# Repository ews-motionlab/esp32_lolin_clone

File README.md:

# esp32_lolin_clone
Design files for a PCB replicating the functionality and shape of the ESP32 lolin32 board.

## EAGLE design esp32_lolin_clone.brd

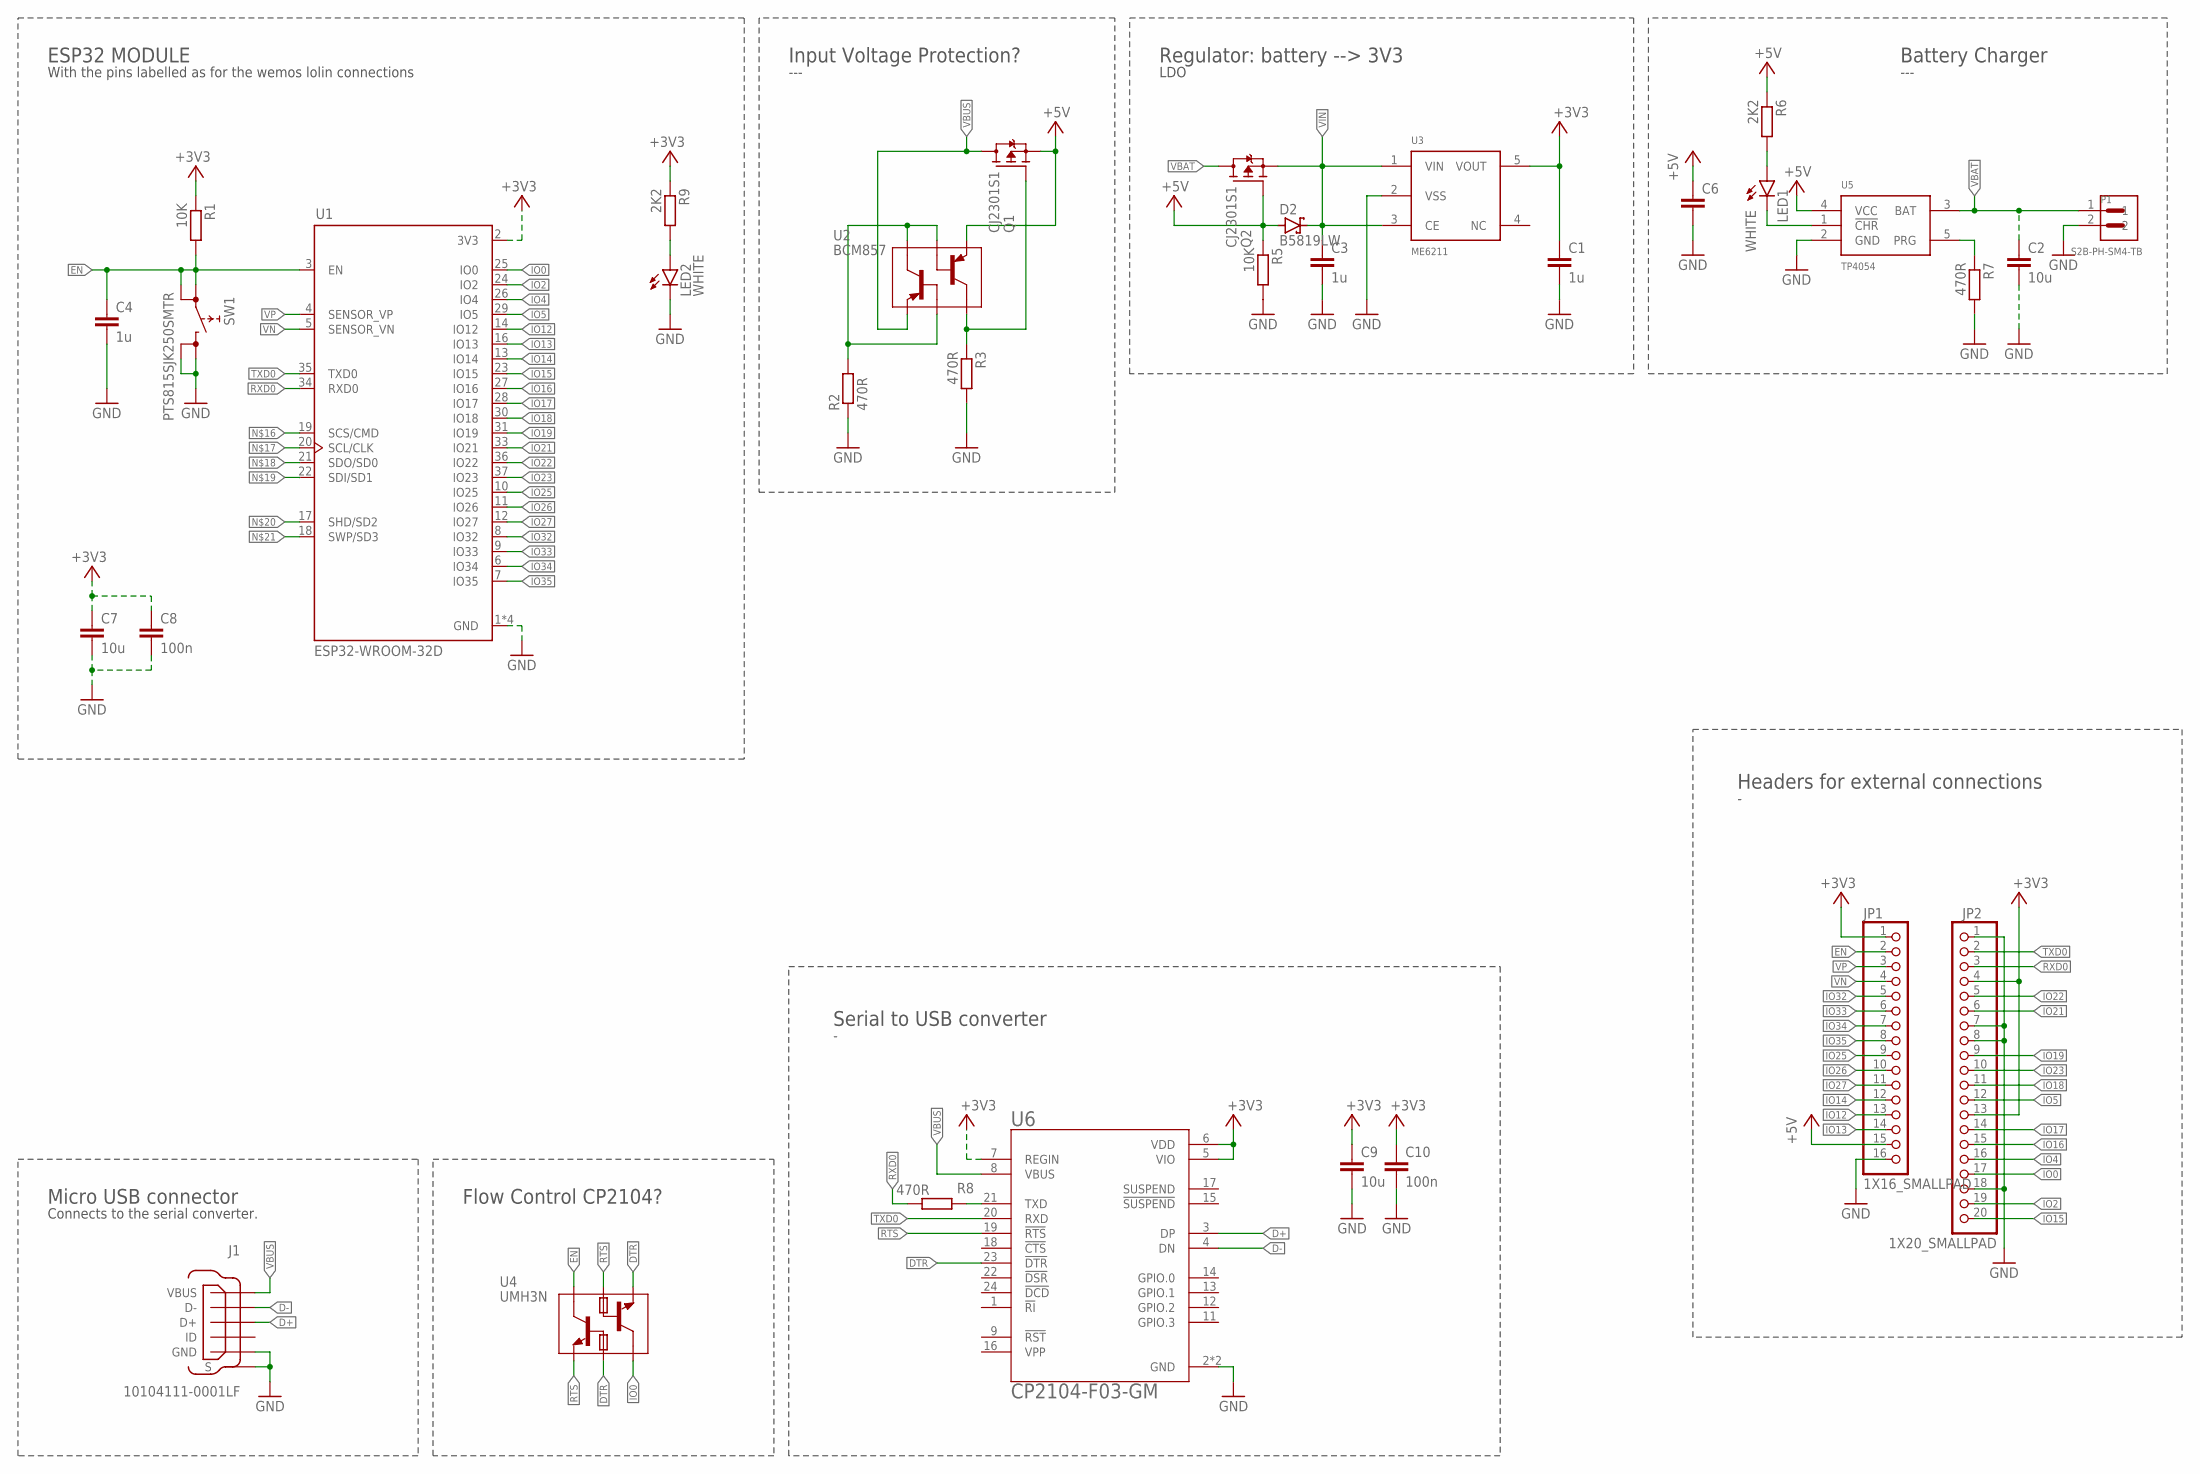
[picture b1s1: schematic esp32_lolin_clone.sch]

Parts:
C1, C3, C4: 1u; C0603K
C2, C7, C9: 10u; C0603K
C6: C-EUC0603K; C0603K
C8, C10: 100n; C0603K
D2: B5819LW; SOD123
J1: 10104111-0001LF; FRAMATOME_10104111-0001LF
JP1: 1X16_SMALLPAD; 1X16
JP2: 1X20_SMALLPAD; 1X20
LED1, LED2: WHITE; CHIP-LED0603
P1: S2B-PH-SM4-TB; JST_S2B-PH-SM4-TB
Q1, Q2: CJ2301S1; SOT23
R1, R5: 10K; R0603
R2, R3, R7, R8: 470R; R0603
R6, R9: 2K2; R0603
SW1: PTS815SJK250SMTR
U1: ESP32-WROOM-32D; MODULE_ESP32-WROOM-32D
U2: BCM857; SOT363_INFINEON
U3: ME6211; SOT23-5
U4: UMH3N; SOT363_INFINEON
U5: TP4054; SOT23-5
U6: CP2104-F03-GM; QFN50P400X400X80-25N

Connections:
+3V3: C1.1, C7.1, C8.1, C9.1, C10.1, JP1.1, JP2.4, JP2.13, R1.1, R9.1, U1.2 (3V3), U3.5 (VOUT), U6.5 (VIO), U6.6 (VDD), U6.7 (REGIN)
+5V: C6.1, D2.2 (A), JP1.15, Q1.2 (S), Q2.1 (G), R5.1, R6.1, U2.4 (E2), U5.4 (VCC)
D+: J1.3 (D+), U6.3 (DP)
D-: J1.2 (D-), U6.4 (DN)
DTR: U4.2 (B1), U4.4 (E2), U6.23 (!DTR)
EN: C4.1, JP1.2, R1.2, SW1.1 (0), SW1.2 (0), U1.3 (EN), U4.6 (C1)
GND: C1.2, C2.2, C3.2, C4.2, C6.2, C7.2, C8.2, C9.2, C10.2, J1.5 (GND), J1.6 (S), J1.7 (S), J1.8 (S), J1.9 (S), JP1.16, JP2.1, JP2.7, JP2.8, JP2.18, LED2.C, P1.2, R2.1, R3.2, R5.2, R7.2, SW1.3 (1), SW1.4 (1), U1.1 (GND), U1.15 (GND), U1.38 (GND), U1.39 (GND), U3.2 (VSS), U5.2 (GND), U6.2 (GND), U6.25 (GND)
IO0: JP2.17, U1.25 (IO0), U4.3 (C2)
IO2: JP2.19, U1.24 (IO2)
IO4: JP2.16, U1.26 (IO4)
IO5: JP2.12, U1.29 (IO5)
IO12: JP1.13, U1.14 (IO12)
IO13: JP1.14, U1.16 (IO13)
IO14: JP1.12, U1.13 (IO14)
IO15: JP2.20, U1.23 (IO15)
IO16: JP2.15, U1.27 (IO16)
IO17: JP2.14, U1.28 (IO17)
IO18: JP2.11, U1.30 (IO18)
IO19: JP2.9, U1.31 (IO19)
IO21: JP2.6, U1.33 (IO21)
IO22: JP2.5, U1.36 (IO22)
IO23: JP2.10, U1.37 (IO23)
IO25: JP1.9, U1.10 (IO25)
IO26: JP1.10, U1.11 (IO26)
IO27: JP1.11, U1.12 (IO27)
IO32: JP1.5, U1.8 (IO32)
IO33: JP1.6, U1.9 (IO33)
IO34: JP1.7, U1.6 (IO34)
IO35: JP1.8, U1.7 (IO35)
unnamed: R8.1, U6.21 (TXD)
unnamed: LED2.A, R9.2
unnamed: LED1.C, U5.1 (!CHR)
unnamed: LED1.A, R6.2
unnamed: R2.2, U2.2 (B1), U2.5 (B2), U2.6 (C1)
unnamed: Q1.1 (G), R3.1, U2.3 (C2)
unnamed: R7.1, U5.5 (PRG)
RTS: U4.1 (E1), U4.5 (B2), U6.19 (!RTS)
RXD0: JP2.3, R8.2, U1.34 (RXD0)
TXD0: JP2.2, U1.35 (TXD0), U6.20 (RXD)
VBAT: C2.1, P1.1, Q2.3 (D), U5.3 (BAT)
VBUS: J1.1 (VBUS), Q1.3 (D), U2.1 (E1), U6.8 (VBUS)
VIN: C3.1, D2.1 (C), Q2.2 (S), U3.1 (VIN), U3.3 (CE)
VN: JP1.4, U1.5 (SENSOR_VN)
VP: JP1.3, U1.4 (SENSOR_VP)

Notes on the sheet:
ESP32 MODULE
With the pins labelled as for the wemos lolin connections
Regulator: battery --> 3V3
LDO
Battery Charger
---
Serial to USB converter
Micro USB connector
Connects to the serial converter.
Input Voltage Protection?
Headers for external connections
Flow Control CP2104?

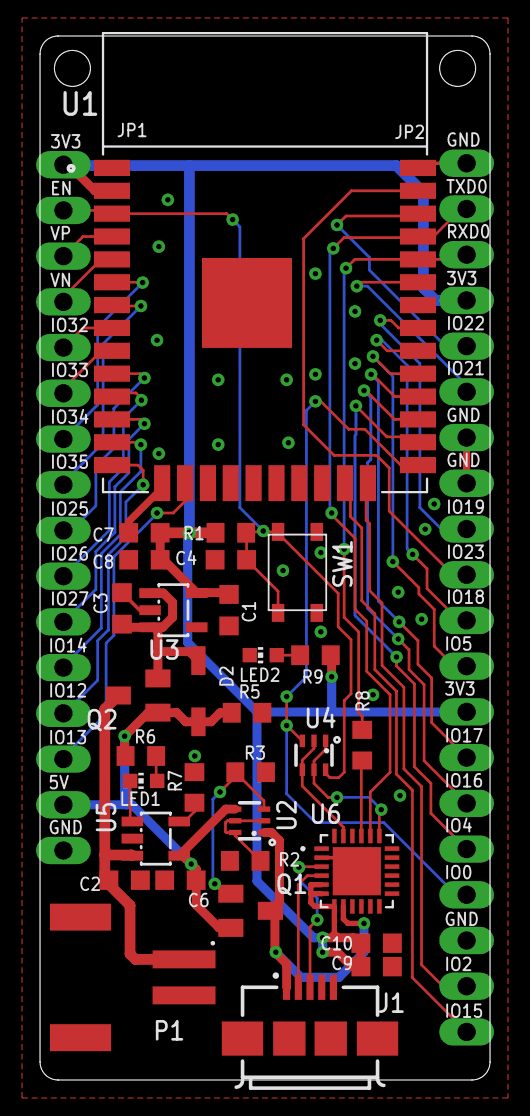
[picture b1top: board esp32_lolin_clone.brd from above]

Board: 2 copper layers, 25.0 x 58.0 mm, 34 parts (1 on the bottom side), 44 nets.

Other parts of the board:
U$1: RE_LOGO_10MM

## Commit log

2020-01-18 Add Schematic and Board design files.
2020-01-20 Routing and changing position of some components.
2021-02-08 - Finish first routing attempt. - Add notes to schematic.
2021-02-08 - set traces to the correct size.
2021-02-08 - check part designators are readable.
2021-02-08 - Add BOM as exported from EAGLE.
2021-02-09 - Finish BOM, modify BOM related issues in schematic.
2021-02-09 - Fix critical error 5V connection missing.
2021-02-12 - As sent to manufacture on 13.12.2021
2021-04-23 - Add a test protocol for the PCB.
2021-04-23 - Change device reference BCM857, so it really matches the footprint at the board.
2021-04-26 - FIX CRITICAL ERROR: Battery connector pins were swapped.
2023-02-20 - Add labels on silk for all pins on top and bottom. - remove lines between pins to improve visibility of pin names.
